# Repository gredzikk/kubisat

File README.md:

# KubiSat: An Open-Source Pico-Satellite Project

Welcome to the KubiSat project! This repository contains all the necessary files to build your own small satellite based on the Raspberry Pi Pico, along with the corresponding ground station firmware. This project was originally conceived as an engineering thesis and has been open-sourced to be useful to a wider community.

## Project Structure

The repository is organized into several key directories:

-   [**`software/`**](software/): Firmware, shared protocol/radio code, and host tooling.
    -   [**`kubisat_firmware/`**](software/kubisat_firmware/): Satellite firmware. See the [firmware README](software/kubisat_firmware/readme.md).
    -   [**`ground_firmware/`**](software/ground_firmware/): Ground station LoRa↔UART bridge. See the [ground README](software/ground_firmware/readme.md).
    -   [**`common/`**](software/common/): Shared LoRa driver and protocol helpers (CRC, frame markers, sync word).
    -   [**`kubisat_operator/`**](software/kubisat_operator/): Avalonia/.NET operator GUI for talking to the ground station over serial.
    -   Status: [`software/FIRMWARE_STATUS.md`](software/FIRMWARE_STATUS.md), protocol: [`software/commands.md`](software/commands.md).
-   [**`hardware/`**](hardware/): KiCad project files for the satellite's printed circuit boards (PCBs), including the main board, power board, and sensor board.
-   [**`case_stl/`**](case_stl/): Contains the STL files for the 3D-printable satellite chassis.
-   [**`doc/`**](doc/): A collection of datasheets for the main components used in the project.

## Features

### Satellite (`kubisat_firmware`)

-   **Modular Architecture:** Code is organized into libraries for communications, sensors, power management, and data logging.
-   **Data Logging:** Uses the `pico-vfs` library to log telemetry and events to an SD card.
-   **LoRa Communication:** Sends and receives data frames using a LoRa module for long-range communication.
-   **Remote Commands:** Supports a command protocol for remote operation and diagnostics.
-   **Automated Build:** Uses CMake for a managed build process with automatic versioning.

### Ground Station (`ground_firmware`)

-   **LoRa-UART Bridge:** Relays messages between a host computer (via USB/Serial) and the satellite (via LoRa).
-   **Simple Addressing:** Ensures messages are correctly routed between the ground station and the satellite.
-   **Signal Strength Reporting:** Can be triggered to report the RSSI and SNR of received packets.

## Getting Started

To get started with building and flashing the firmware, please refer to the detailed instructions in the README files for each respective firmware:

-   **For the satellite:** [kubisat_firmware/readme.md](software/kubisat_firmware/readme.md)
-   **For the ground station:** [ground_firmware/readme.md](software/ground_firmware/readme.md)

The hardware can be manufactured using the KiCad files in the [`hardware/`](hardware/) directory, and the case can be 3D printed using the files in [`case_stl/`](case_stl/).

## Contributing

Contributions are welcome! Please read our [contributing guidelines](CONTRIBUTING.md) to get started. You can report bugs, suggest features, or submit pull requests.

## License

This project is licensed under the MIT License. See the [LICENSE](LICENSE) file for details.

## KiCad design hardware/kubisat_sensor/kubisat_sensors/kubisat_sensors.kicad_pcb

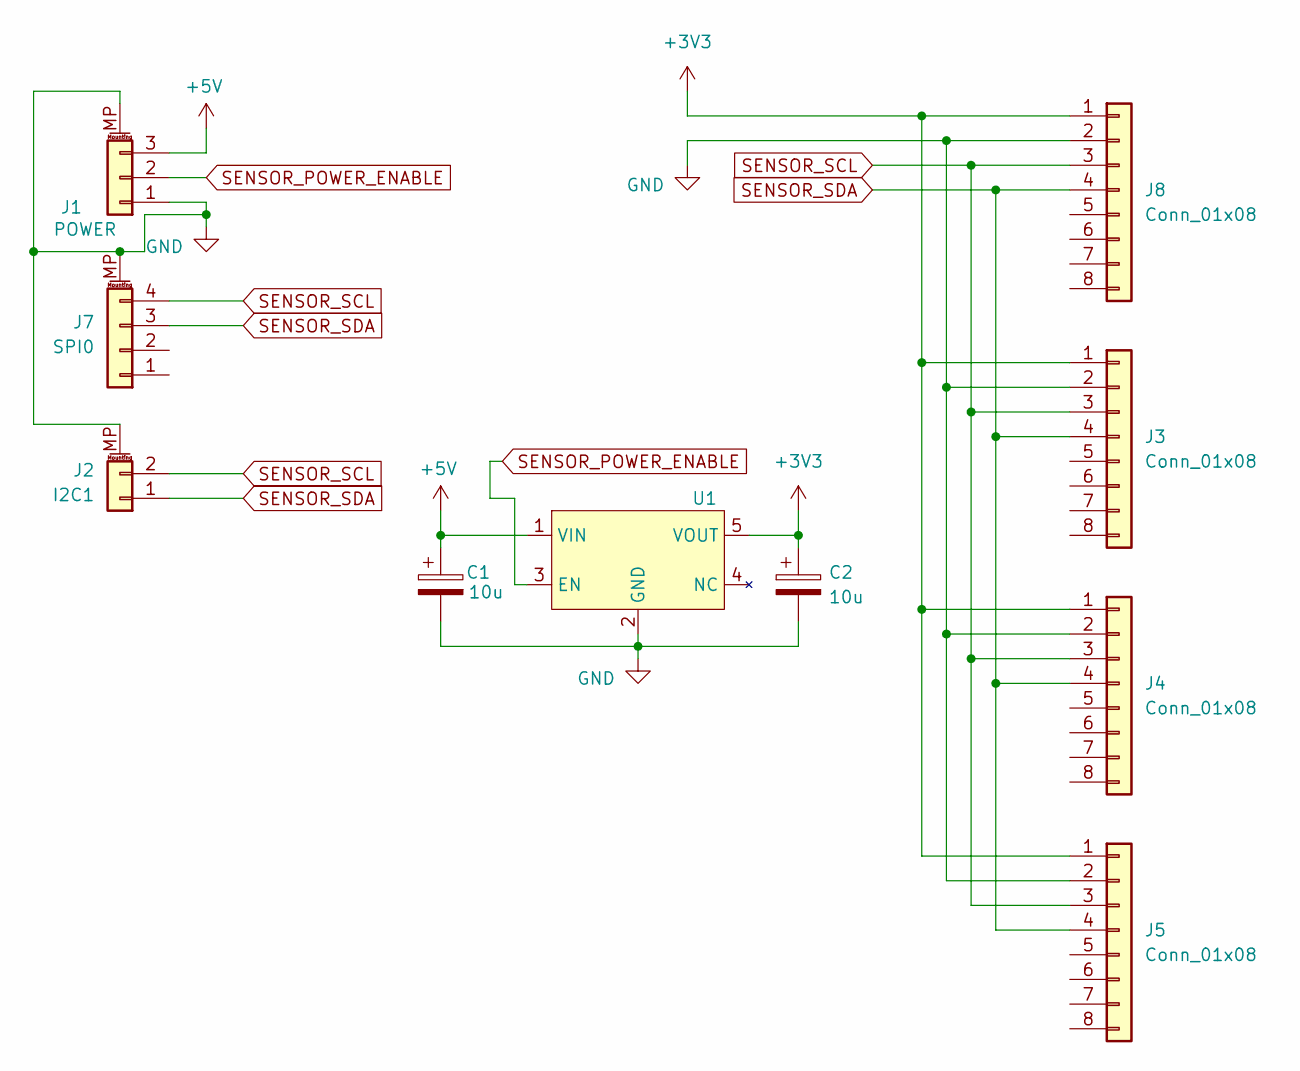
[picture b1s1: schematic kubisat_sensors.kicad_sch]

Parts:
C1, C2: 10u; CP_EIA-3216-18_Kemet-A
J1: POWER; JST_PH_S3B-PH-SM4-TB_1x03-1MP_P2.00mm_Horizontal
J2: I2C1; JST_PH_S2B-PH-SM4-TB_1x02-1MP_P2.00mm_Horizontal
J3, J4, J5, J8: Conn_01x08; PinSocket_1x08_P2.54mm_Vertical
J7: SPI0; JST_PH_S4B-PH-SM4-TB_1x04-1MP_P2.00mm_Horizontal
U1: SOT-23-5

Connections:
+3V3: C2.1, J3.1, J4.1, J5.1, J8.1, U1.5 (VOUT)
+5V: C1.1, J1.3, U1.1 (VIN)
GND: C1.2, C2.2, J1.1, J1.MP (MountPin), J2.MP (MountPin), J3.2, J4.2, J5.2, J7.MP (MountPin), J8.2, U1.2 (GND)
SENSOR_POWER_ENABLE: J1.2, U1.3 (EN)
SENSOR_SCL: J2.2, J3.3, J4.3, J5.3, J7.4, J8.3
SENSOR_SDA: J2.1, J3.4, J4.4, J5.4, J7.3, J8.4

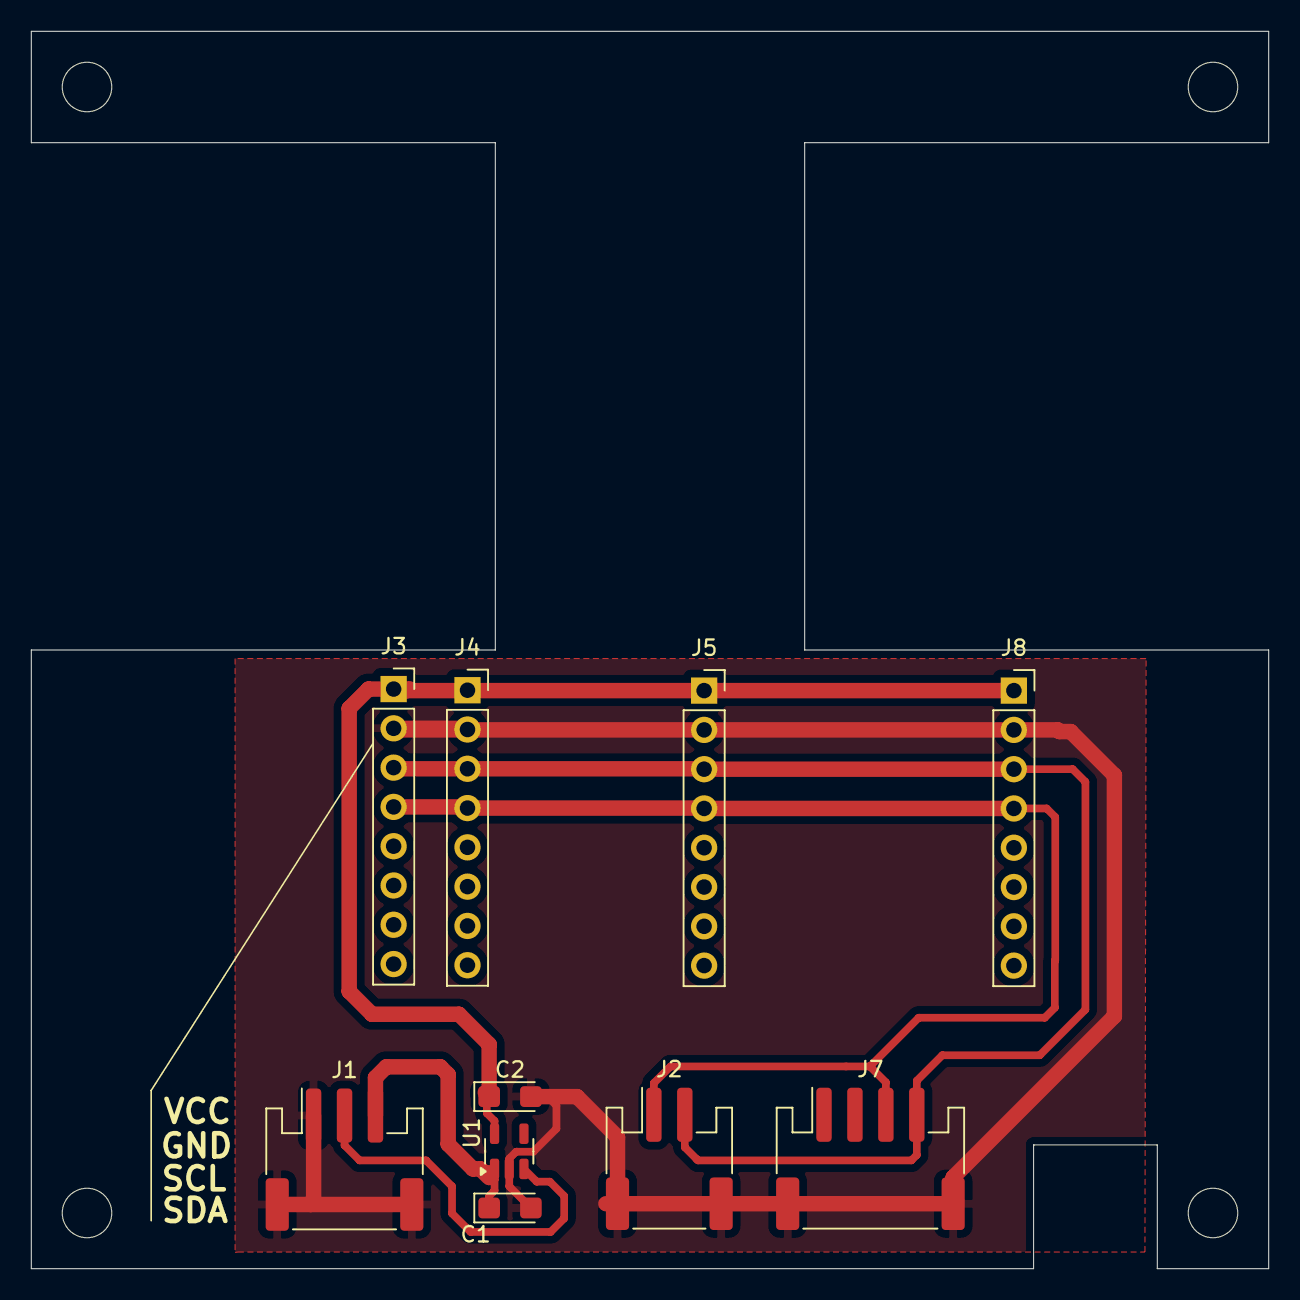
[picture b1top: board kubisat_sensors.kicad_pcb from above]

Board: 2 copper layers, 80.0 x 80.0 mm, 14 parts (0 on the bottom side), 6 nets.

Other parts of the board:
H1, H1#2, H1#3, H1#4: MountingHole; MountingHole_3.2mm_M3_DIN965

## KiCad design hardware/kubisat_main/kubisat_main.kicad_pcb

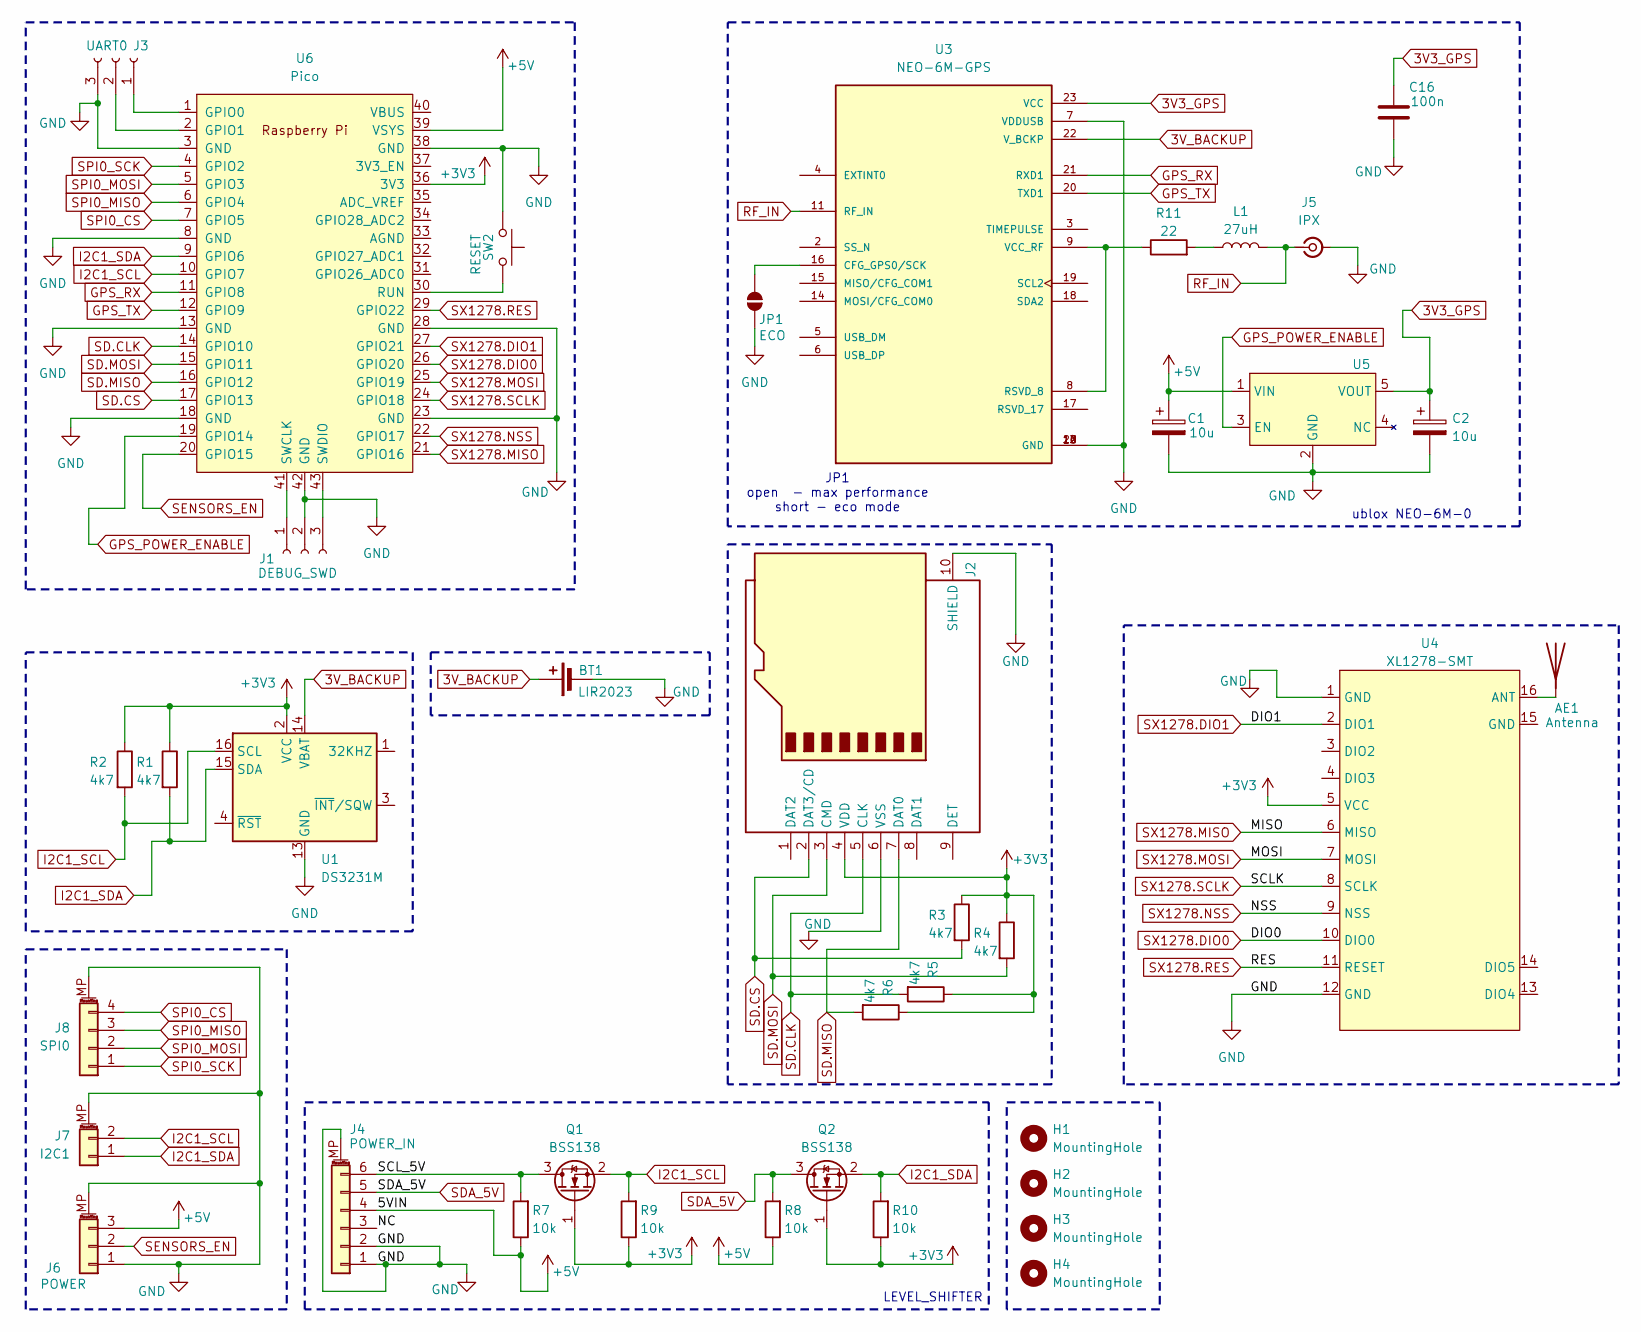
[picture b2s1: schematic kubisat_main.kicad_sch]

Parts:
AE1: Antenna
BT1: LIR2023; BatteryHolder_Keystone_106_1x20mm
C1, C2: 10u; CP_EIA-3216-18_Kemet-A
C16: 100n; C_0805_2012Metric
H1, H2, H3, H4: MountingHole; MountingHole_3.2mm_M3_DIN965
J1: DEBUG_SWD; PinHeader_1x03_P2.54mm_Horizontal
J2: Micro_SD_Card_Det1; J_SD_Card-micro_socket_A
J3: UART0; PinHeader_1x03_P2.54mm_Horizontal
J4: POWER_IN; JST_PH_S6B-PH-SM4-TB_1x06-1MP_P2.00mm_Horizontal
J5: IPX; U.FL_Hirose_U.FL-R-SMT-1_Vertical
J6: POWER; JST_PH_S3B-PH-SM4-TB_1x03-1MP_P2.00mm_Horizontal
J7: I2C1; JST_PH_S2B-PH-SM4-TB_1x02-1MP_P2.00mm_Horizontal
J8: SPI0; JST_PH_S4B-PH-SM4-TB_1x04-1MP_P2.00mm_Horizontal
JP1: ECO; SolderJumper-2_P1.3mm_Open_RoundedPad1.0x1.5mm
L1: 27uH; L_0805_2012Metric
Q1, Q2: BSS138; SOT-23
R1, R2, R3, R4, R5, R6: 4k7; R_0805_2012Metric
R7, R8, R9, R10: 10k; R_0805_2012Metric
R11: 22; R_0805_2012Metric
SW2: RESET; SW_Push_1P1T_NO_CK_KMR2
U1: DS3231M; SOIC-16W_7.5x10.3mm_P1.27mm
U3: NEO-6M-GPS; ublox_NEO; PARTREV R15
U4: XL1278-SMT
U5: SOT-23-5
U6: Pico; RPi_Pico_SMD_TH

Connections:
3V3_GPS: C2.1, C16.1, U3.23 (VCC), U5.5 (VOUT)
3V_BACKUP: BT1.1 (+), U1.14 (VBAT), U3.22 (V_BCKP)
+3V3: J2.4 (VDD), Q1.1 (G), Q2.1 (G), R1.1, R2.1, R3.1, R4.1, R5.1, R6.1, R9.1, R10.1, U1.2 (VCC), U4.5 (VCC), U6.36 (3V3)
+5V: C1.1, J4.4, J6.3, R7.1, R8.1, U5.1 (VIN), U6.39 (VSYS)
/NC: J4.3
/SCL_5V: J4.6, Q1.3 (D), R7.2
GND: BT1.2 (-), C1.2, C2.2, C16.2, J1.2, J2.6 (VSS), J2.10 (SHIELD), J3.3, J4.1, J4.2, J4.MP (MountPin), J5.2 (Ext), J6.1, J6.MP (MountPin), J7.MP (MountPin), J8.MP (MountPin), JP1.2 (B), SW2.1, U1.5 (GND), U1.6 (GND), U1.7 (GND), U1.8 (GND), U1.9 (GND), U1.10 (GND), U1.11 (GND), U1.12 (GND), U1.13 (GND), U3.7 (VDDUSB), U3.10 (GND), U3.12 (GND), U3.13 (GND), U3.24 (GND), U4.1 (GND), U4.12 (GND), U5.2 (GND), U6.3 (GND), U6.8 (GND), U6.13 (GND), U6.18 (GND), U6.23 (GND), U6.28 (GND), U6.38 (GND), U6.42 (GND)
GPS_POWER_ENABLE: U5.3 (EN), U6.19 (GPIO14)
GPS_RX: U3.21 (RXD1), U6.11 (GPIO8)
GPS_TX: U3.20 (TXD1), U6.12 (GPIO9)
I2C1_SCL: J7.2, Q1.2 (S), R2.2, R9.2, U1.16 (SCL), U6.10 (GPIO7)
I2C1_SDA: J7.1, Q2.2 (S), R1.2, R10.2, U1.15 (SDA), U6.9 (GPIO6)
unnamed: AE1.1, U4.16 (ANT)
unnamed: J1.1, U6.41 (SWCLK)
unnamed: J1.3, U6.43 (SWDIO)
unnamed: J3.1, U6.1 (GPIO0)
unnamed: J3.2, U6.2 (GPIO1)
unnamed: JP1.1 (A), U3.16 (CFG_GPS0/SCK)
unnamed: L1.1, R11.2
unnamed: R11.1, U3.8 (RSVD_8), U3.9 (VCC_RF)
unnamed: SW2.2, U6.30 (RUN)
RF_IN: J5.1 (In), L1.2, U3.11 (RF_IN)
SD.CLK: J2.5 (CLK), R5.2, U6.14 (GPIO10)
SD.CS: J2.2 (DAT3/CD), R3.2, U6.17 (GPIO13)
SD.MISO: J2.7 (DAT0), R6.2, U6.16 (GPIO12)
SD.MOSI: J2.3 (CMD), R4.2, U6.15 (GPIO11)
SDA_5V: J4.5, Q2.3 (D), R8.2
SENSORS_EN: J6.2, U6.20 (GPIO15)
SPI0_CS: J8.4, U6.7 (GPIO5)
SPI0_MISO: J8.3, U6.6 (GPIO4)
SPI0_MOSI: J8.2, U6.5 (GPIO3)
SPI0_SCK: J8.1, U6.4 (GPIO2)
SX1278.DIO0: U4.10 (DIO0), U6.26 (GPIO20)
SX1278.DIO1: U4.2 (DIO1), U6.27 (GPIO21)
SX1278.MISO: U4.6 (MISO), U6.21 (GPIO16)
SX1278.MOSI: U4.7 (MOSI), U6.25 (GPIO19)
SX1278.NSS: U4.9 (NSS), U6.22 (GPIO17)
SX1278.RES: U4.11 (RESET), U6.29 (GPIO22)
SX1278.SCLK: U4.8 (SCLK), U6.24 (GPIO18)

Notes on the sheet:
JP1 open - max performance short - eco mode
ublox NEO-6M-0
LEVEL_SHIFTER

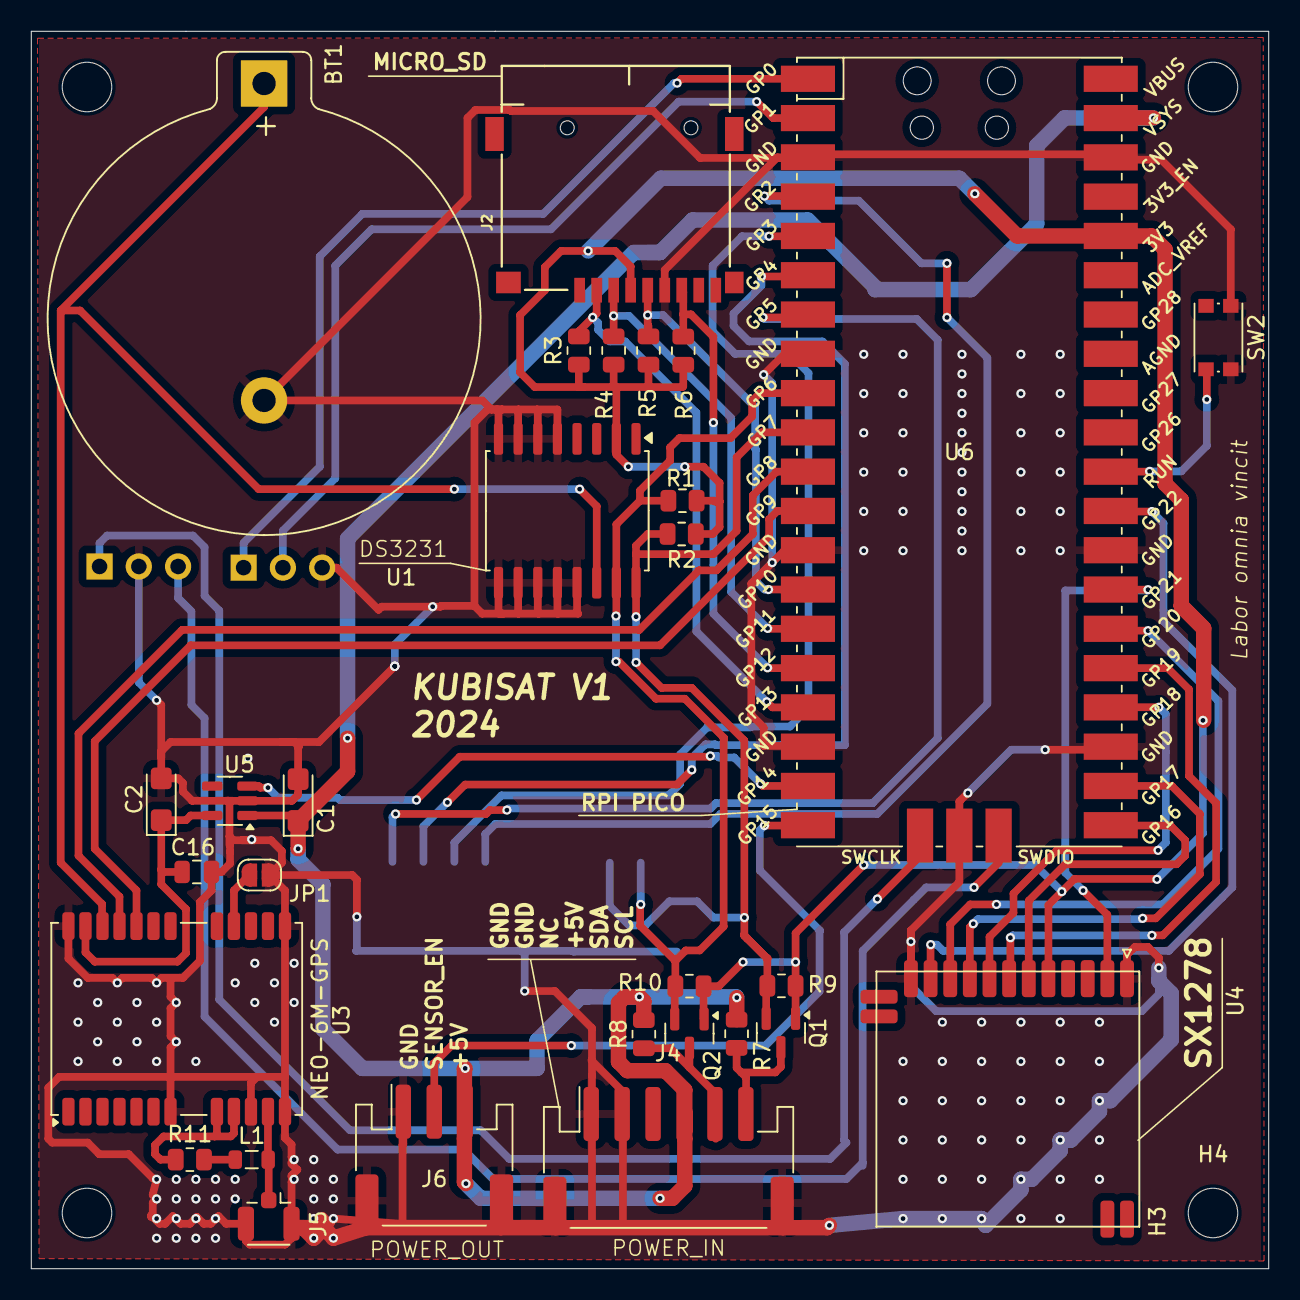
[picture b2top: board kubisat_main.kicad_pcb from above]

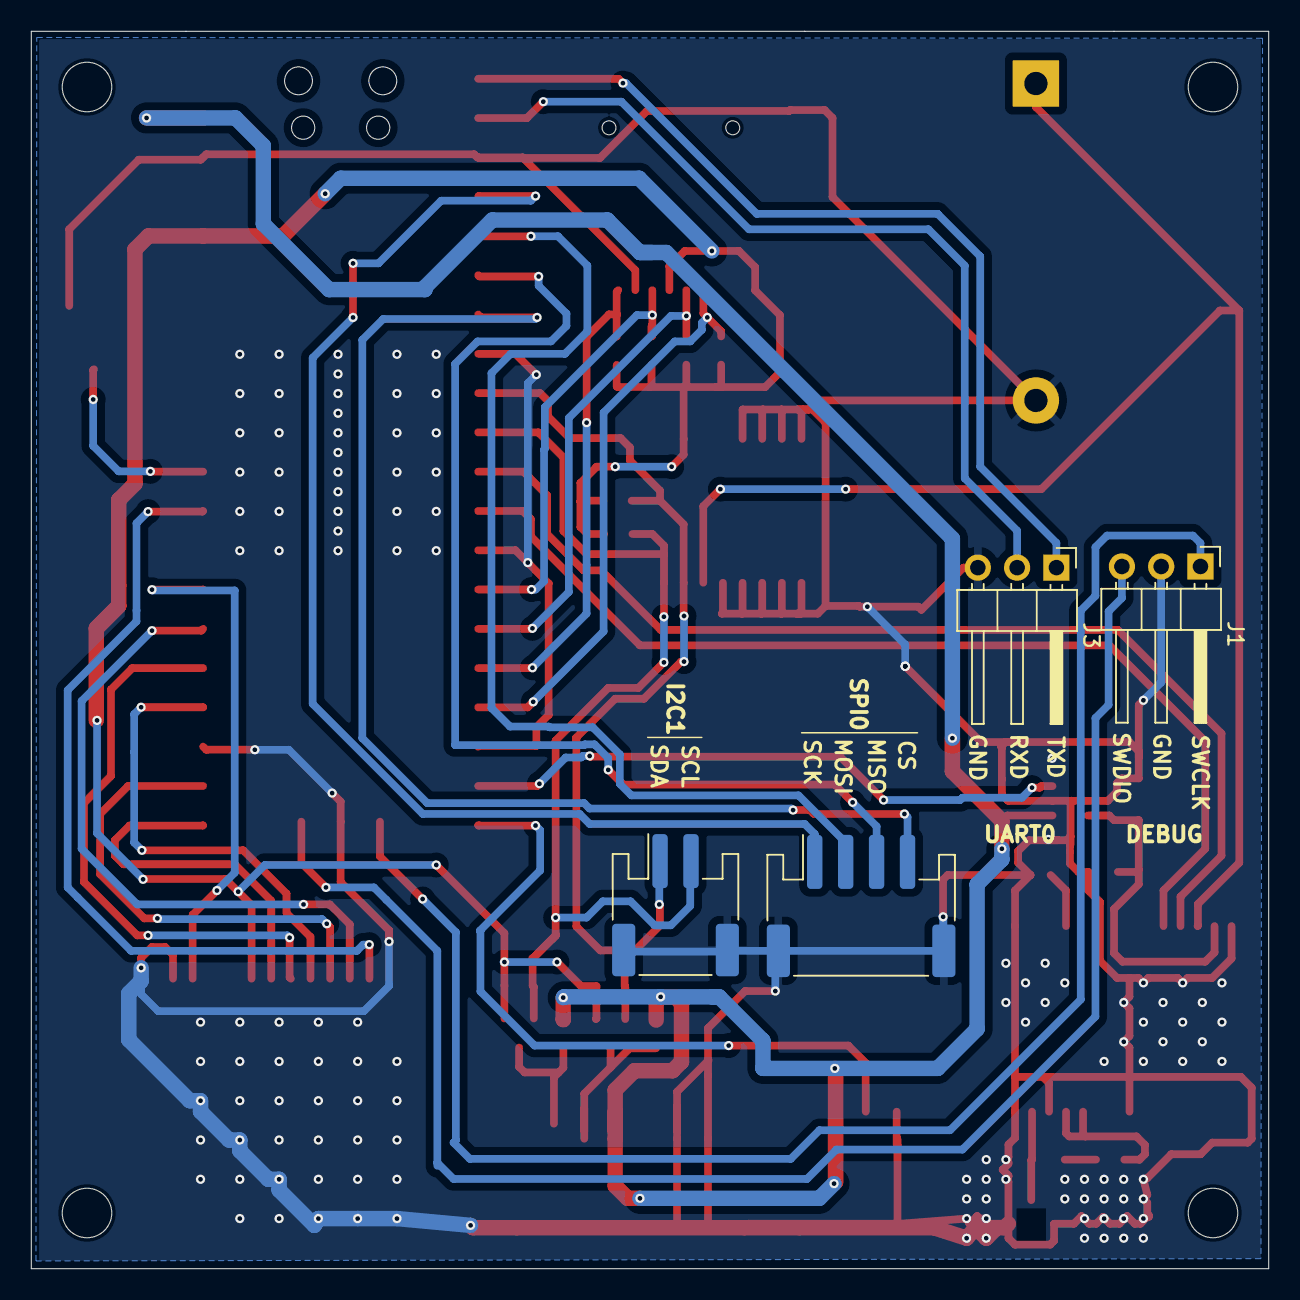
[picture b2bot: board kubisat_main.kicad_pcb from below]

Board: 2 copper layers, 80.0 x 80.0 mm, 37 parts (4 on the bottom side), 37 nets.

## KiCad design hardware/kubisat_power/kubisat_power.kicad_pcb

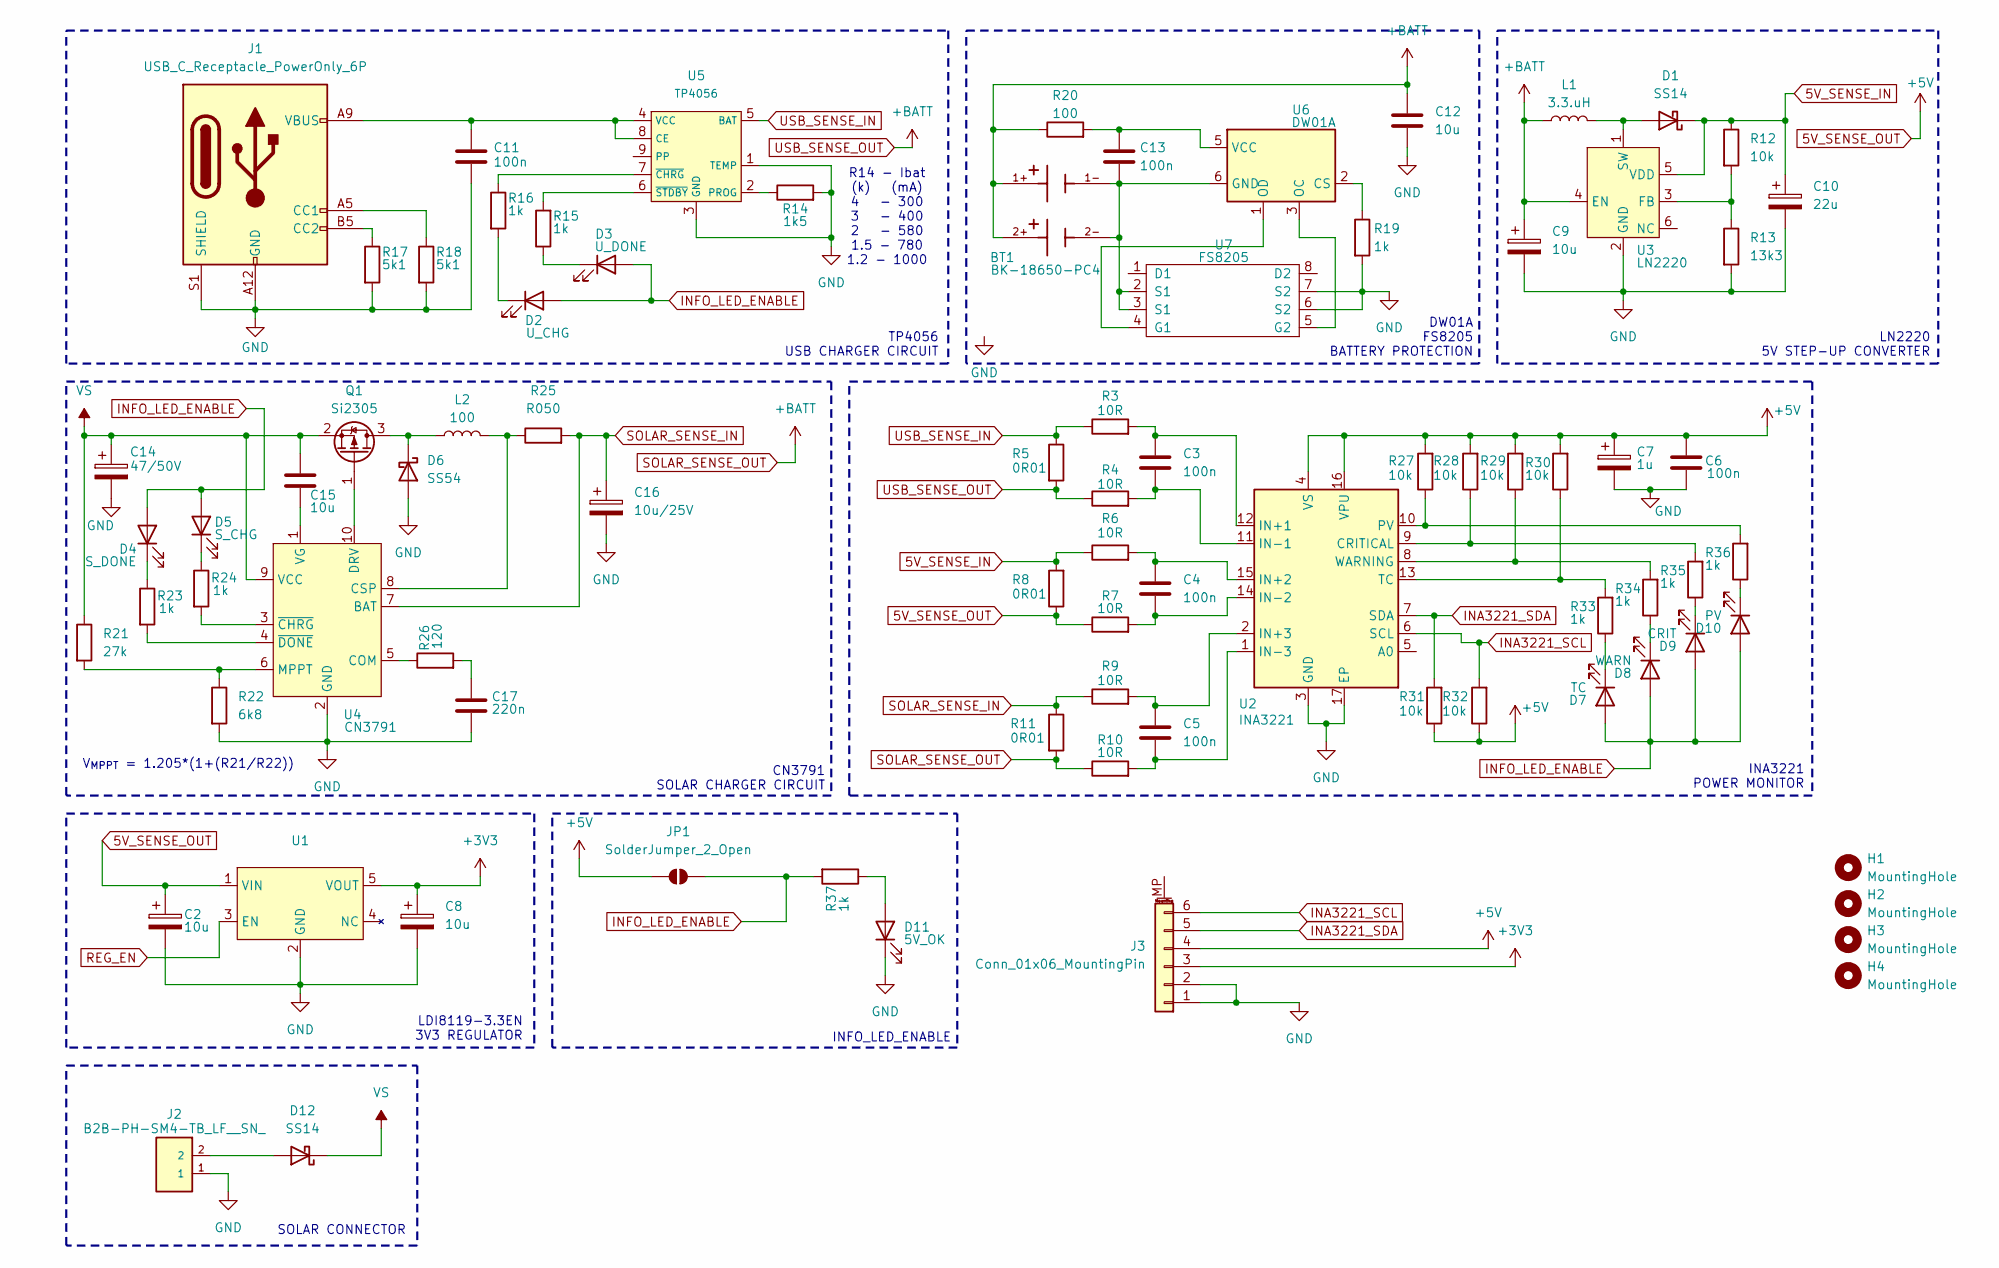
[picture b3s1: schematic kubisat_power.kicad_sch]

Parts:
BT1: BK-18650-PC4; BAT_BK-18650-PC4; PARTREV K
C2, C8: 10u; CP_Elec_4x5.4
C3, C4, C5, C6, C11, C13: 100n; C_0805_2012Metric
C7: 1u; CP_Elec_4x5.4
C9: 10u; C_1206_3216Metric
C10: 22u; C_1206_3216Metric
C12, C15: 10u; C_0805_2012Metric
C14: 47/50V; C_Elec_6.3x5.8
C16: 10u/25V; C_1210_3225Metric
C17: 220n; C_0805_2012Metric
D1, D12: SS14; D_SMA
D2: U_CHG; LED_0805_2012Metric
D3: U_DONE; LED_0805_2012Metric
D4: S_DONE; LED_0805_2012Metric
D5: S_CHG; LED_0805_2012Metric
D6: SS54; D_SMA
D7: TC; LED_0805_2012Metric
D8: WARN; LED_0805_2012Metric
D9: CRIT; LED_0805_2012Metric
D10: PV; LED_0805_2012Metric
D11: 5V_OK; LED_0805_2012Metric
H1, H2, H3, H4: MountingHole; MountingHole_3.2mm_M3_DIN965
J1: USB_C_Receptacle_PowerOnly_6P; GCT_USB4140-GF-0230-C_REV0.4
J2: B2B-PH-SM4-TB_LF__SN_
J3: Conn_01x06_MountingPin; JST_PH_S6B-PH-SM4-TB_1x06-1MP_P2.00mm_Horizontal
JP1: SolderJumper_2_Open; SolderJumper-2_P1.3mm_Open_RoundedPad1.0x1.5mm
L1: 3.3.uH; L_Cenker_CKCS5040
L2: 100; L_Bourns_SRP7028A_7.3x6.6mm
Q1: Si2305; SOT-23
R3, R4, R6, R7, R9, R10: 10R; R_0805_2012Metric
R5, R8, R11: 0R01; R_2512_6332Metric_Pad1.40x3.35mm_HandSolder
R12, R27, R28, R29, R30, R31, R32: 10k; R_0805_2012Metric
R13: 13k3; R_0805_2012Metric
R14: 1k5; R_0805_2012Metric
R15, R16, R19, R23, R24, R33, R34, R35, R36, R37: 1k; R_0805_2012Metric
R17, R18: 5k1; R_0805_2012Metric
R20: 100; R_0805_2012Metric
R21: 27k; R_0805_2012Metric
R22: 6k8; R_0805_2012Metric
R25: R050; R_2512_6332Metric_Pad1.40x3.35mm_HandSolder
R26: 120; R_0805_2012Metric
U1: SOT-23-5
U2: INA3221; Texas_RGV0016A_VQFN-16-1EP_4x4mm_P0.65mm_EP2.1x2.1mm
U3: LN2220; TSOT-23-6_HandSoldering
U4: CN3791; SSOP-10-1EP_3.9x4.9mm_P1mm_EP2.1x3.3mm
U5: TP4056; SOIC-8-1EP_3.9x4.9mm_P1.27mm_EP2.29x3mm
U6: DW01A; SOT-23-6
U7: FS8205; TSSOP-8_3x3mm_P0.65mm; LCSC C32254

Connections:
5V_SENSE_IN: C10.1, D1.1 (K), R6.1, R8.2, R12.1, U3.5 (VDD)
+3V3: C8.1, J3.3, U1.5 (VOUT)
GND: C2.2, C6.2, C7.2, C8.2, C9.2, C10.2, C11.2, C12.2, C14.2, C16.2, C17.2, D6.2 (A), D11.1 (K), J1.A12 (GND), J1.B12 (GND), J1.S1 (SHIELD), J2.1, J3.1, J3.2, R13.2, R14.2, R17.2, R18.2, R19.2, R22.2, U1.2 (GND), U2.3 (GND), U2.17 (EP), U3.2 (GND), U4.2 (GND), U5.1 (TEMP), U5.3 (GND), U7.6 (S2), U7.7 (S2)
INA3221_SCL: J3.6, R32.2, U2.6 (SCL)
INA3221_SDA: J3.5, R31.2, U2.7 (SDA)
INFO_LED_ENABLE: D2.2 (A), D3.2 (A), D4.2 (A), D5.2 (A), D7.2 (A), D8.2 (A), D9.2 (A), D10.2 (A), JP1.2 (B), R37.2
unnamed: C17.1, R26.2
unnamed: D1.2 (A), L1.2, U3.1 (SW)
unnamed: D2.1 (K), R16.2
unnamed: D3.1 (K), R15.1
unnamed: D4.1 (K), R23.1
unnamed: D5.1 (K), R24.1
unnamed: D6.1 (K), L2.1, Q1.3 (D)
unnamed: D7.1 (K), R33.1
unnamed: D8.1 (K), R34.1
unnamed: D9.1 (K), R35.1
unnamed: D10.1 (K), R36.1
unnamed: D11.2 (A), R37.1
unnamed: D12.2 (A), J2.2
unnamed: J1.A5 (CC1), R18.1
unnamed: J1.B5 (CC2), R17.1
unnamed: Q1.1 (G), U4.10 (DRV)
unnamed: R28.1, R35.2, U2.9 (CRITICAL)
unnamed: C3.1, R3.2, U2.12 (IN+1)
unnamed: C4.1, R6.2, U2.15 (IN+2)
unnamed: C5.1, R9.2, U2.2 (IN+3)
unnamed: C3.2, R4.2, U2.11 (IN-1)
unnamed: C4.2, R7.2, U2.14 (IN-2)
unnamed: C5.2, R10.2, U2.1 (IN-3)
unnamed: R27.1, R36.2, U2.10 (PV)
unnamed: R30.1, R33.2, U2.13 (TC)
unnamed: R29.1, R34.2, U2.8 (WARNING)
unnamed: R12.2, R13.1, U3.3 (FB)
unnamed: R26.1, U4.5 (COM)
unnamed: L2.2, R25.1, U4.8 (CSP)
unnamed: R21.2, R22.1, U4.6 (MPPT)
unnamed: C15.2, U4.1 (VG)
unnamed: R24.2, U4.3 (~CHRG)
unnamed: R23.2, U4.4 (~DONE)
unnamed: C11.1, J1.A9 (VBUS), J1.B9 (VBUS), U5.4 (VCC), U5.8 (CE)
unnamed: R14.1, U5.2 (PROG)
unnamed: R16.1, U5.7 (~CHRG)
unnamed: R15.2, U5.6 (~STDBY)
unnamed: R19.1, U6.2 (CS)
unnamed: BT1.1-, BT1.2-, C13.2, U6.6 (GND), U7.2 (S1), U7.3 (S1)
unnamed: U6.3 (OC), U7.5 (G2)
unnamed: U6.1 (OD), U7.4 (G1)
unnamed: C13.1, R20.2, U6.5 (VCC)
REG_EN: U1.3 (EN)
SOLAR_SENSE_IN: C16.1, R9.1, R11.1, R25.2, U4.7 (BAT)
USB_SENSE_IN: R3.1, R5.1, U5.5 (BAT)
VS: C14.1, C15.1, D12.1 (K), Q1.2 (S), R21.1, U4.9 (VCC)

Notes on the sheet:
INFO_LED_ENABLE
CN3791 SOLAR CHARGER CIRCUIT
R14 - Ibat (k) (mA) 4 - 300 3 - 400 2 - 580 1.5 - 780 1.2 - 1000
LN2220 5V STEP-UP CONVERTER
LDI8119-3.3EN 3V3 REGULATOR
TP4056 USB CHARGER CIRCUIT
V_{MPPT} = 1.205*(1+(R21/R22))
DW01A FS8205 BATTERY PROTECTION
SOLAR CONNECTOR
INA3221 POWER MONITOR

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
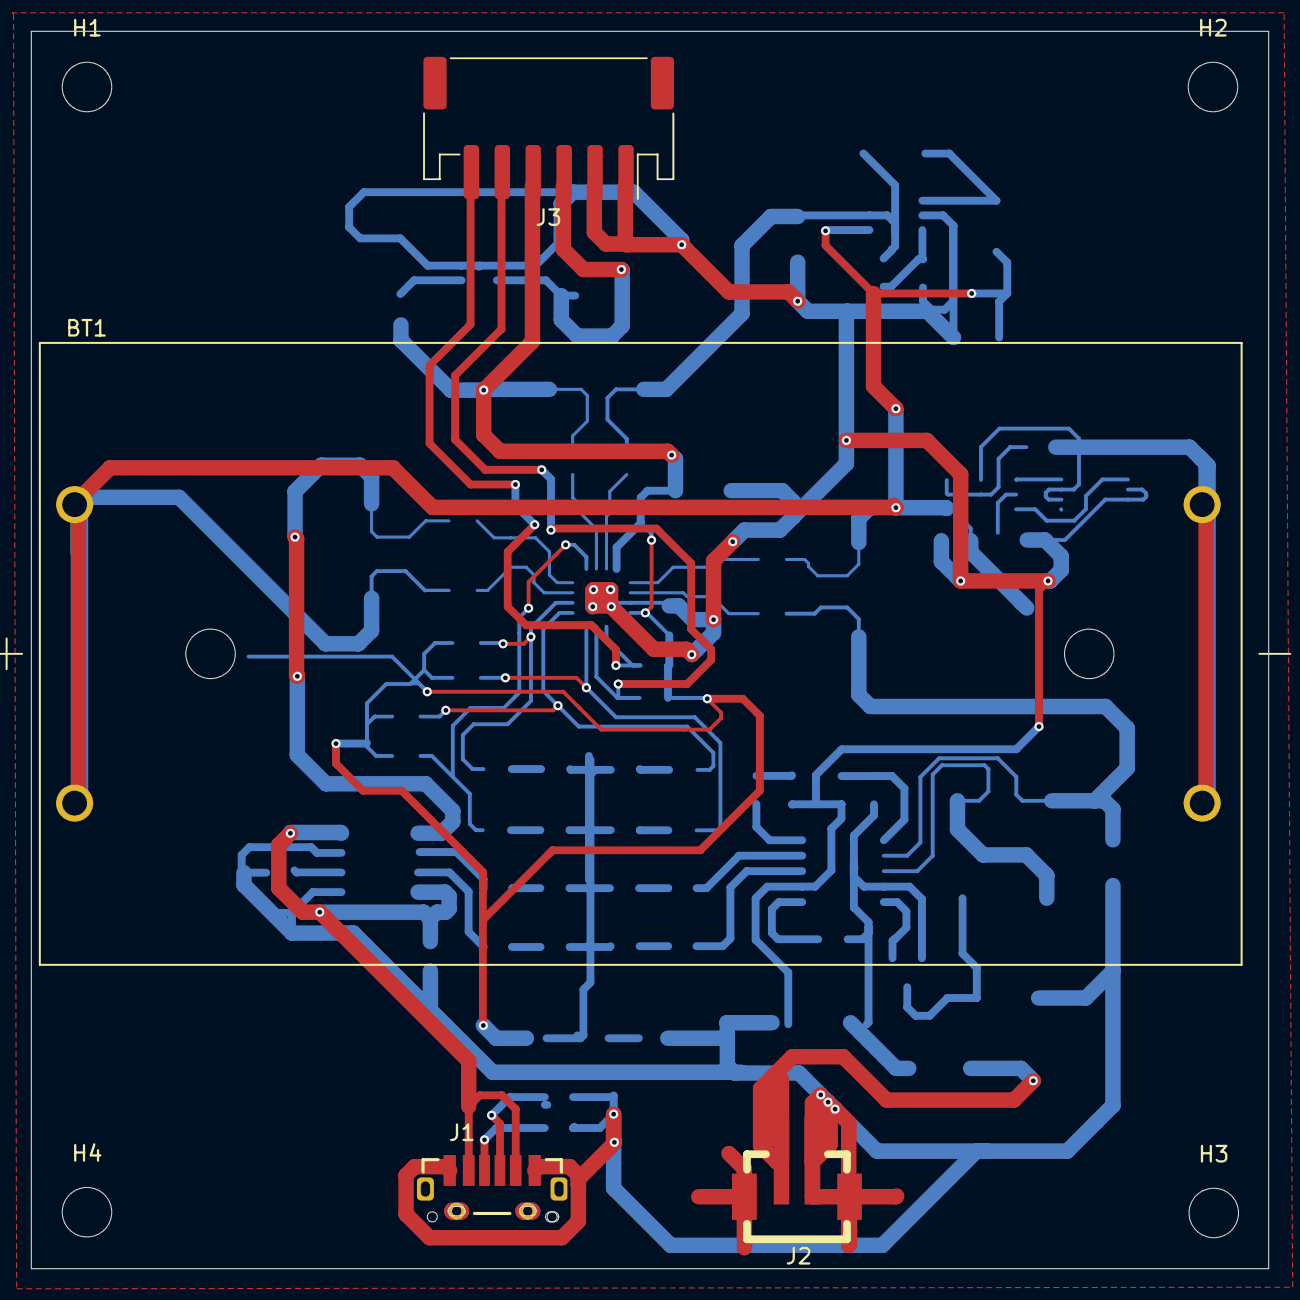
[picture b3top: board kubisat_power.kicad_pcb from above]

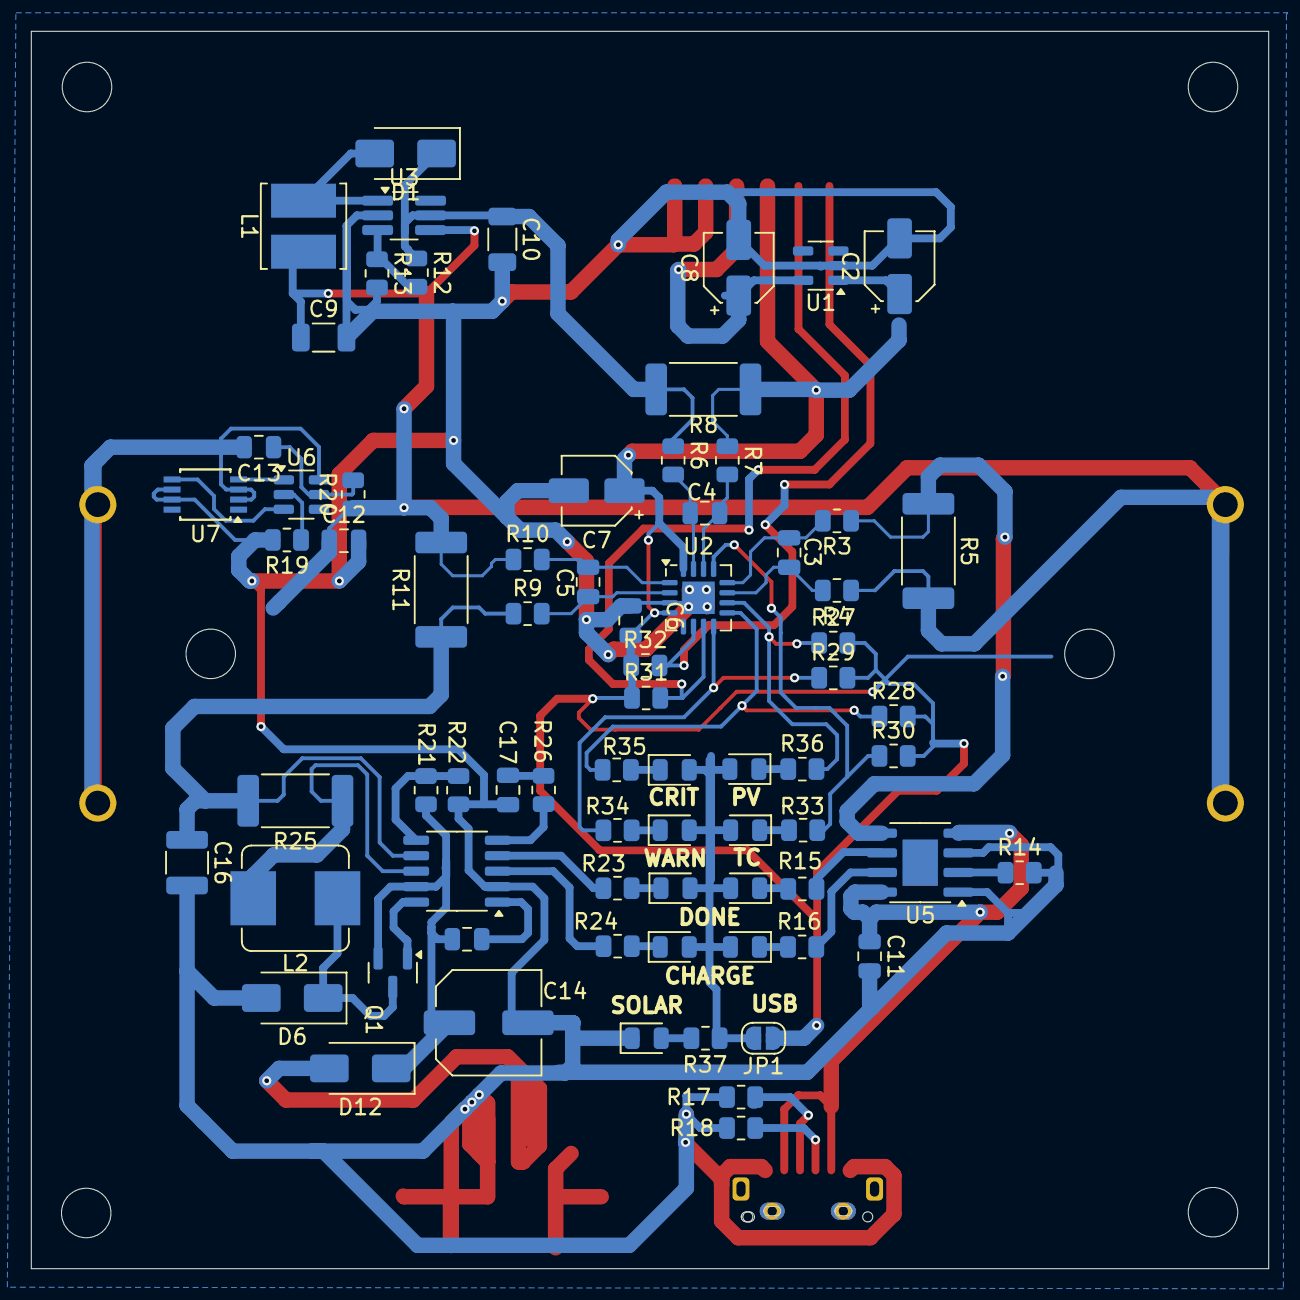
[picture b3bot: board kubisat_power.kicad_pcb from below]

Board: 2 copper layers, 80.0 x 80.0 mm, 82 parts (74 on the bottom side), 53 nets.

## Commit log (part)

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2024-08-20 first commit with folder structure and complete 3d model
2024-08-20 first commit with dir structure and complete 3d model
2024-08-22 changed model
2024-08-22 3d model v2, added BOM
2024-08-24 added f3z project files
2024-08-24 changed side model structure
2024-09-11 added image and pdf sources, updated schematic
2024-09-26 complete schematic, todo add solar connectors
2024-09-29 changed battery holder
2024-10-01 completed schematic with solar connectors, changed 3v3 regulator
2024-10-02 arranged elements on board, made some traces
2024-10-02 more traces
2024-10-03 complete routing, changed usb and side terminal - this version was ordered in jlcpcb
2024-10-03 added MCU based on arduino zeros ATSAMD21G18A
2024-10-21 added software - ina3221 and camera scripts
2024-10-22 added arduino code, more items on main schematic
2024-10-23 added elements and traces to main pcb
2024-10-24 added microsd footprint
2024-10-24 added pdfs ds and register info to process into uml diagrams
2024-10-24 added base code for data types
2024-10-24 added basic data model structure
2024-10-25 added cpp code
2024-10-28 probably working python version base data types with unit tests
2024-10-28 added new code to serialize and deserialize sensor data to hex format, added not yet working unit tests
2024-10-29 working cpp version, todo add physical sensor data reading to test working of this
2024-10-29 working rp2040 version without excceptions
2024-10-30 working rp2040-zero ina3221 readout, TODO combine this with base-os
2024-10-30 added bmp280 support
2024-11-06 added pico-lora github library and configured to work on 2 separate picos
2024-11-07 working terminal prototype
2024-11-12 added more working libraries to use
2024-11-13 working common interface version
2024-11-15 added elements to cpu schematic
2024-11-15 added pcb elements
2024-11-24 side 3d model
2024-11-25 changed strucutre, split main into 2 sseparate boards
2024-11-26 completed (?) mainboard schematic
2024-11-27 finished main board
2025-01-21 changed folder structure
2025-02-03 changed structure to submodules in software subdirectory
2025-02-03 changed directory structure to subdirectories in /software
2025-02-03 updated submodule reference
2025-02-03 updated main firmware
2025-02-03 update main firmware submodule
2025-02-04 updated submodule kubisat_firmware
2025-02-25 3d model of corner support
2025-02-26 added sensors board
2025-03-18 added 3d models of boards
2025-08-18 cleanup
2025-08-18 commit to one repo
2025-08-18 fixes
2025-08-18 added commands desc
2025-08-18 added main readme
2025-08-18 added photos
2025-08-18 added renders
